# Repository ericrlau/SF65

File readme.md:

# SF65
## A ZMK-Powered BLE Keyboard with visible surface-mount components proudly displayed.

> :warning: **This is an untested project.** Do not use to create your own copy unless you are willing to debug the hardware and/or firmware. 

## Flash bootloader
Bootloader is pre-loaded on assembled pcbs. If you source your own BLE module you will need to unlock the module and flash the bootloader using the Nordic nrf command line tool. 
```
$ nrfjprog --recover --log 
```
```
$ nrfjprog -f nrf52 --program firmware/bootloader/COBO_nrf52840_bootloader-0.3.2-184-g64ea299_s140_6.1.1.hex
```

------------------------------------
## Upload Firmware 

- See ZMK docs for instructions on setting up ZMK and custimizing firmware.  
	* https://zmkfirmware.dev/docs/user-setup/
	* https://zmkfirmware.dev/docs/customization 
- Default *.uf2 files are pre-loaded on assembled pcbs. If you sourced and assembled your own pcb, you can file deafult pre-built firmware here: 
	- https://github.com/ericrlau/COBO-zmk-config/releases

## PCB
- Source files for pcb are in this repo. They are split into three kicad projects:
	- SF65: main pcb, left and right combined. 
	- (ToDo) SF65_Bottom: Bottom cover PCB. 
	- (ToDo) SF65_Plate: Switch plate PCB. 
	- NOTE: KiCad files are created with nightly KiCad 5.99 builds, they are not compatible with current stable release of KiCad 5.
- Bill of materials [Link](https://raw.githack.com/ericrlau/SF65/working/PCB/bom/ibom.html)

## ToDo 
- Test prototypes.
- Create switch plate.
- Create bottom Cover.
- Create bottom foot to angle board.
- Fix silk screen arrow on 1U key to right of spacebar. 

## Images

#### Prototype Build

#### Main PCB

#### FR4 Plate

#### Bottom PCB

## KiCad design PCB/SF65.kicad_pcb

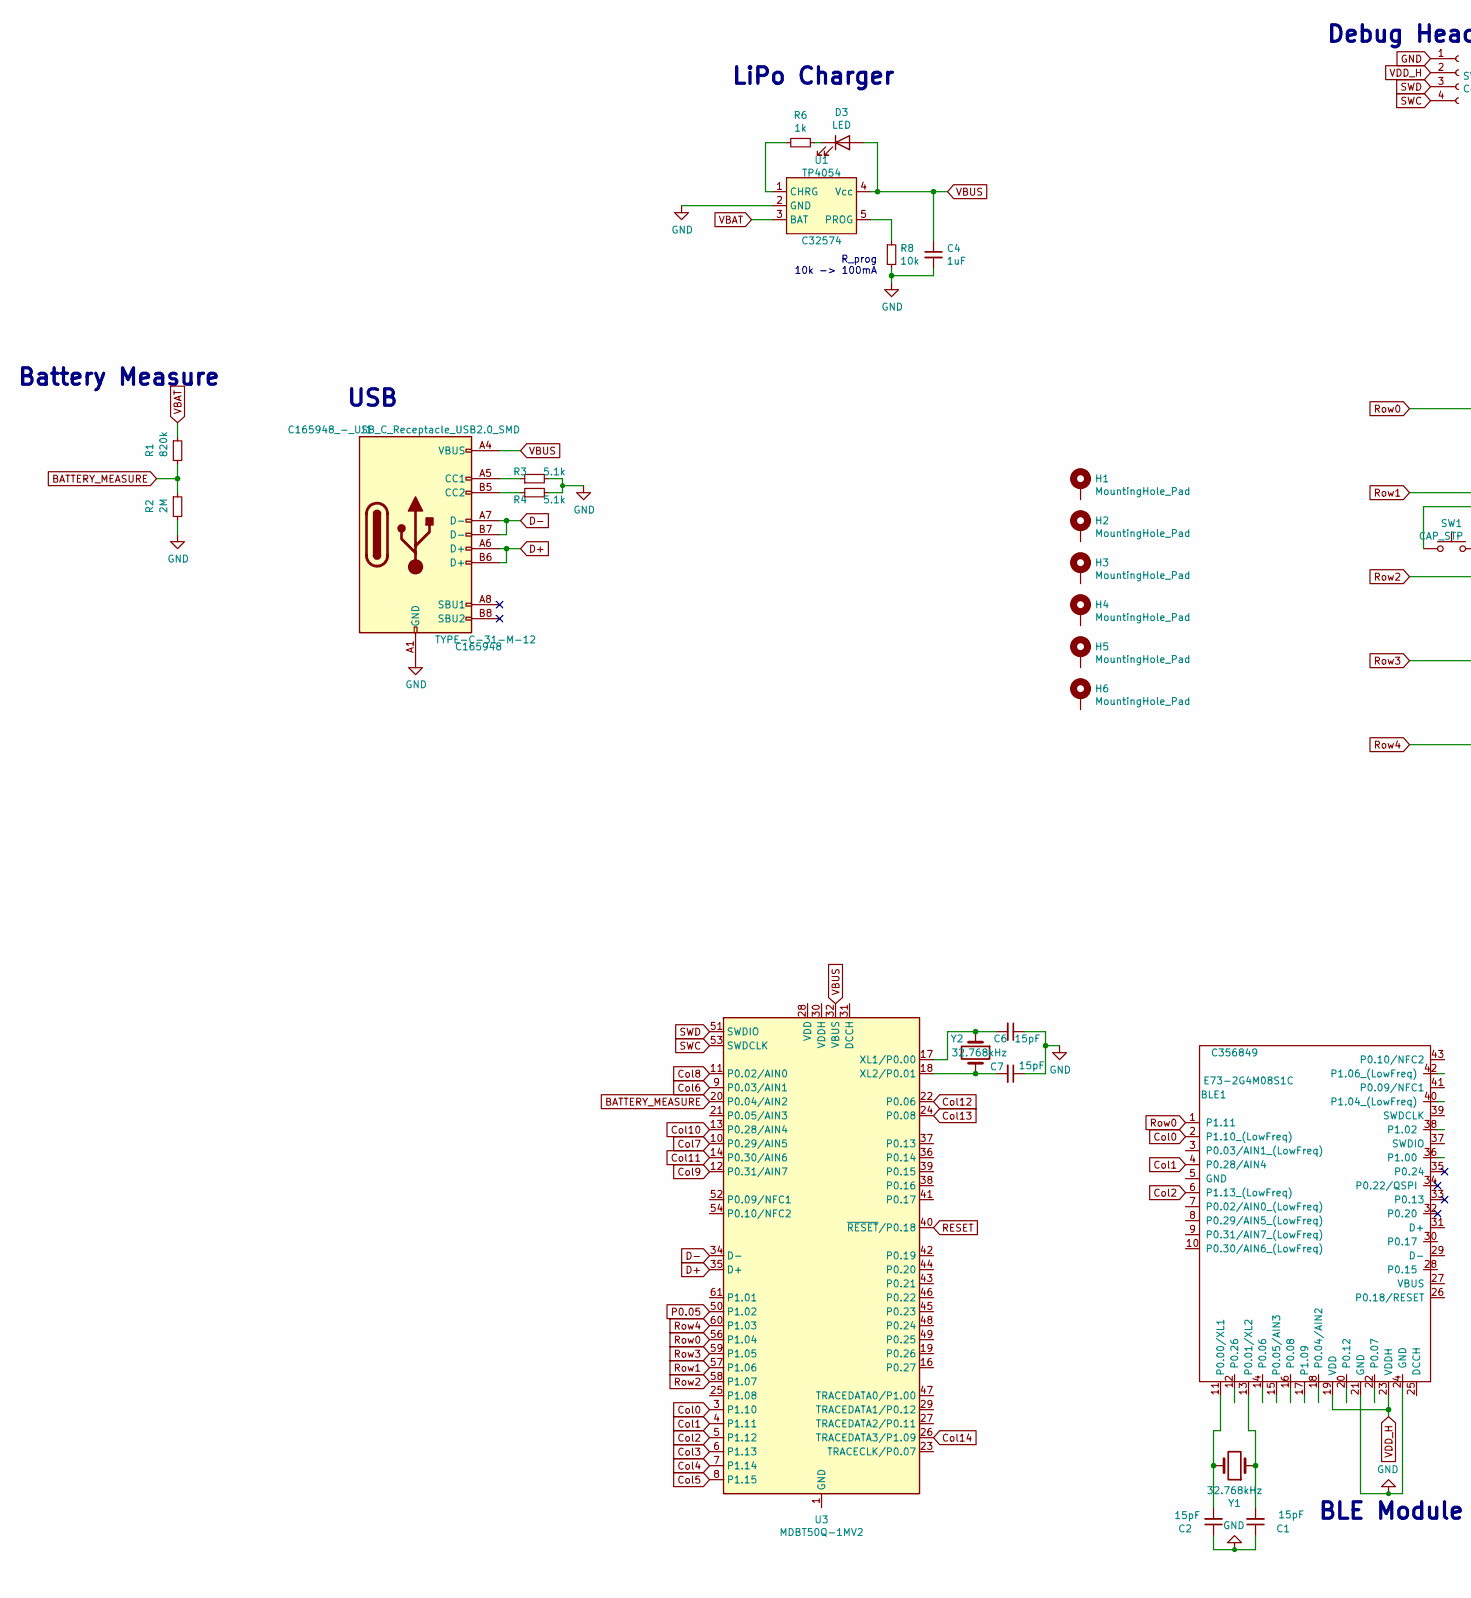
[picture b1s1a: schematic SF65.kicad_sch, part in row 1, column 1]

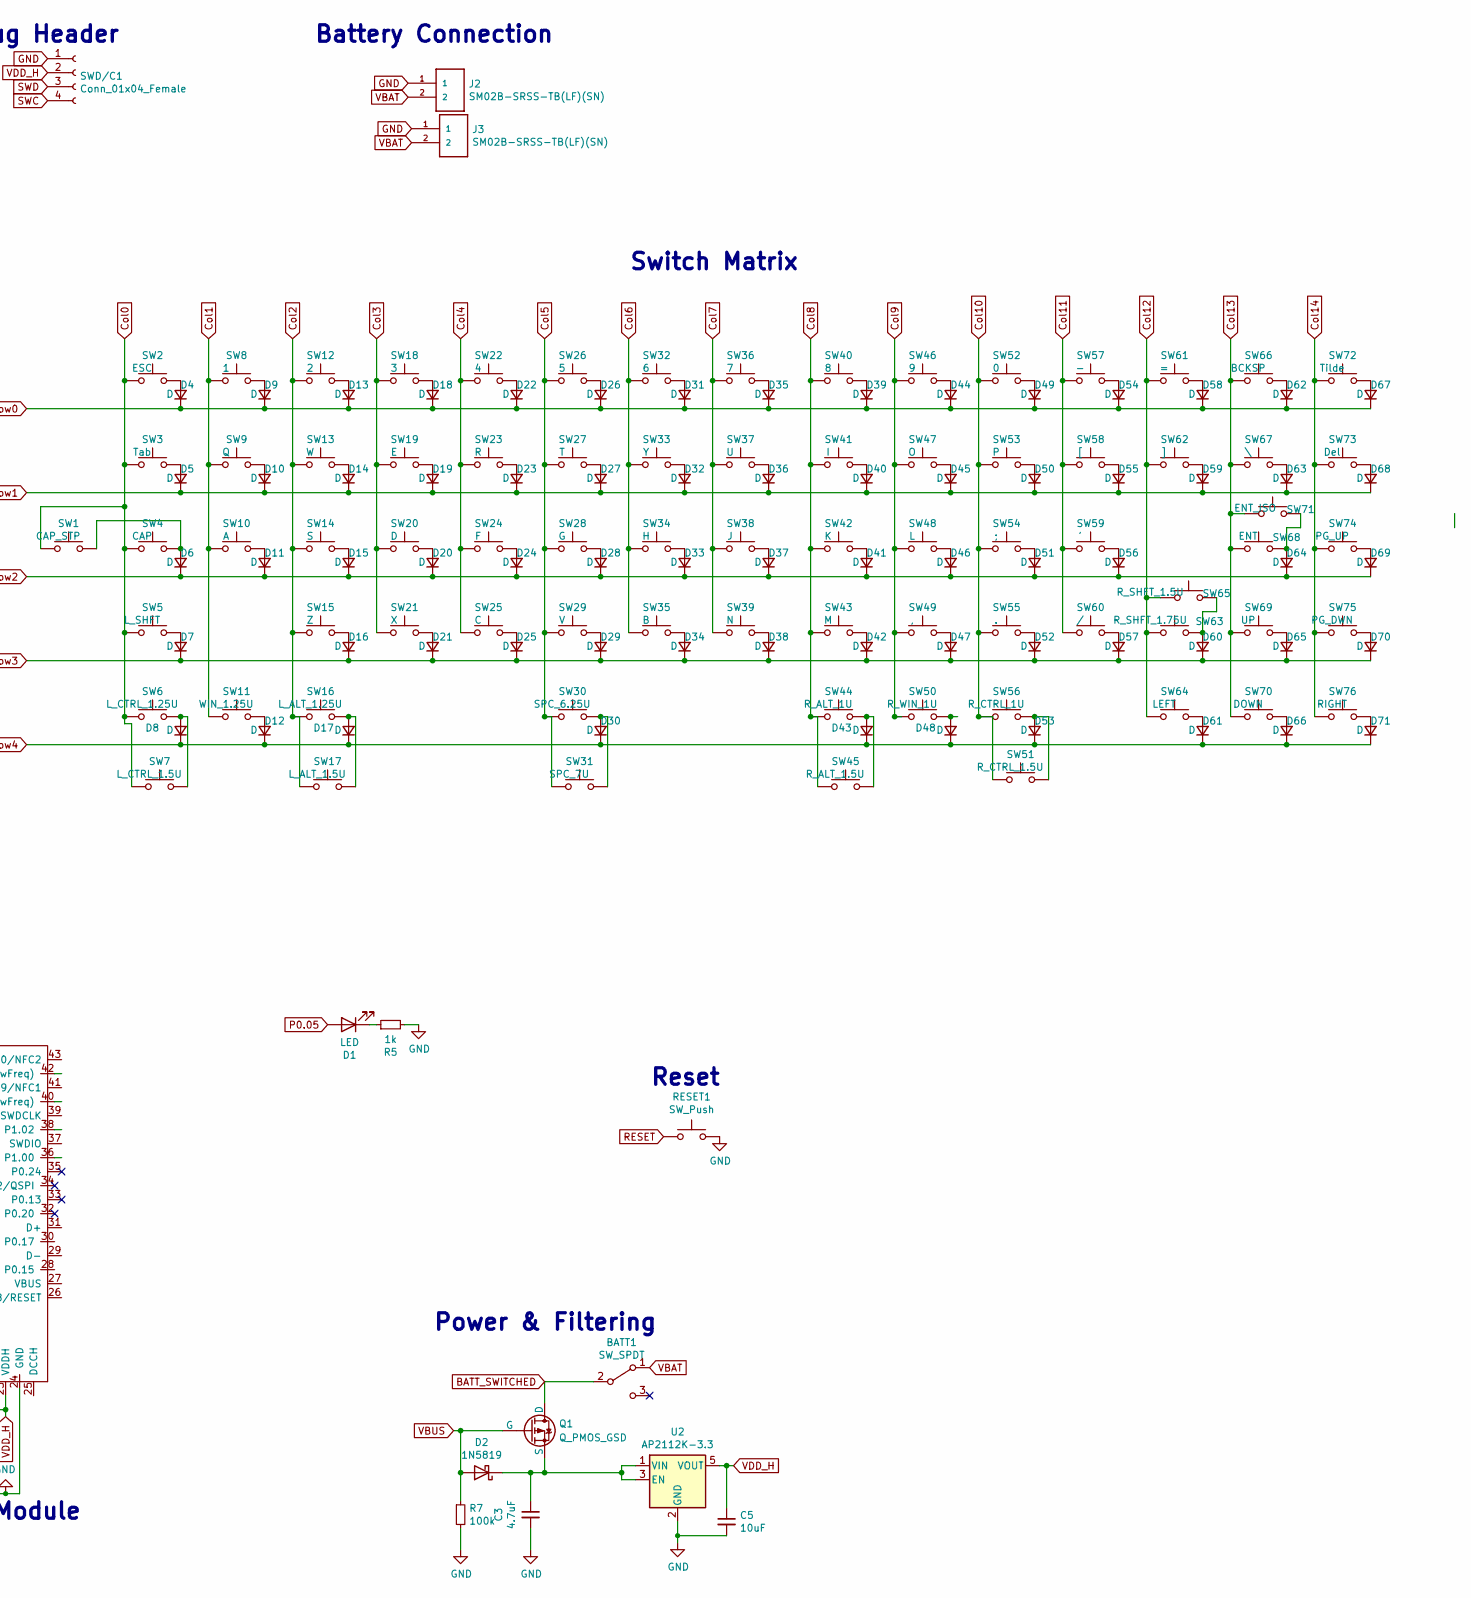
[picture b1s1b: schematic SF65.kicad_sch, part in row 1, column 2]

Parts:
BATT1: SW_SPDT; SW-TH_MSK12C02
BLE1: E73-2G4M08S1C; Manufacturer PN E73-2G4M08S1C; LCSC PN C356849
C1, C2, C6, C7: 15pF; C_0603_1608Metric
C3: 4.7uF; C_0603_1608Metric
C4: 1uF; C_0603_1608Metric
C5: 10uF; C_0603_1608Metric
D1, D3: LED; LED_0603_1608Metric_Pad1.05x0.95mm_HandSolder
D2: 1N5819; D_SOD-323_HandSoldering
D4, D5, D6, D7, D8, D9, D10, D11, D12, D13, D14, D15, D16, D17, D18, D19, D20, D21, D22, D23, D24, D25, D26, D27, D28, D29, D30, D31, D32, D33, D34, D35, D36, D37, D38, D39, D40, D41, D42, D43, D44, D45, D46, D47, D48, D49, D50, D51, D52, D53, D54, D55, D56, D57, D58, D59, D60, D61, D62, D63, D64, D65, D66, D67, D68, D69, D70, D71: D; D_SOD-123
H1, H2, H3, H4, H5, H6: MountingHole_Pad; MountingHole_2.2mm_M2
J1: C165948_-_USB_C_Receptacle_USB2.0_SMD; USB_C_Receptacle_HRO_TYPE-C-31-M-12; Manufacturer PN TYPE-C-31-M-12; LCSC PN C165948
J2: SM02B-SRSS-TB(LF)(SN)
J3: SM02B-SRSS-TB(LF)(SN); PinHeader_1x02_P2.54mm_Vertical
Q1: Q_PMOS_GSD; SOT-23
R1: 820k; R_0603_1608Metric_Pad0.98x0.95mm_HandSolder
R2: 2M; R_0603_1608Metric_Pad0.98x0.95mm_HandSolder
R3, R4: 5.1k; R_0603_1608Metric_Pad0.98x0.95mm_HandSolder
R5, R6: 1k; R_0603_1608Metric_Pad0.98x0.95mm_HandSolder
R7: 100k; R_0603_1608Metric_Pad0.98x0.95mm_HandSolder
R8: 10k; R_0603_1608Metric_Pad0.98x0.95mm_HandSolder
RESET1: SW_Push; SW_SPST_B3U-1000P
SW1: CAP_STP; MX_1.75U_STEPPEDCAPS
SW2: ESC; SW_Cherry_MX_1.00u_PCB
SW3: Tab; SW_Cherry_MX_1.50u_PCB
SW4: CAP; SW_Cherry_MX_1.75u_PCB
SW5: L_SHFT; SW_Cherry_MX_2.25u_PCB
SW6: L_CTRL_1.25U; SW_Cherry_MX_1.25u_PCB
SW7: L_CTRL_1.5U; SW_Cherry_MX_1.50u_PCB
SW8: 1; SW_Cherry_MX_1.00u_PCB
SW9: Q; SW_Cherry_MX_1.00u_PCB
SW10: A; SW_Cherry_MX_1.00u_PCB
SW11: WIN_1.25U; SW_Cherry_MX_1.25u_PCB
SW12: 2; SW_Cherry_MX_1.00u_PCB
SW13: W; SW_Cherry_MX_1.00u_PCB
SW14: S; SW_Cherry_MX_1.00u_PCB
SW15: Z; SW_Cherry_MX_1.00u_PCB
SW16: L_ALT_1.25U; SW_Cherry_MX_1.25u_PCB
SW17: L_ALT_1.5U; SW_Cherry_MX_1.50u_PCB
SW18: 3; SW_Cherry_MX_1.00u_PCB
SW19: E; SW_Cherry_MX_1.00u_PCB
SW20: D; SW_Cherry_MX_1.00u_PCB
SW21: X; SW_Cherry_MX_1.00u_PCB
SW22: 4; SW_Cherry_MX_1.00u_PCB
SW23: R; SW_Cherry_MX_1.00u_PCB
SW24: F; SW_Cherry_MX_1.00u_PCB
SW25: C; SW_Cherry_MX_1.00u_PCB
SW26: 5; SW_Cherry_MX_1.00u_PCB
SW27: T; SW_Cherry_MX_1.00u_PCB
SW28: G; SW_Cherry_MX_1.00u_PCB
SW29: V; SW_Cherry_MX_1.00u_PCB
SW30: SPC_6.25U; SW_Cherry_MX_6.25u_PCB
SW31: SPC_7U; MX_7U
SW32: 6; SW_Cherry_MX_1.00u_PCB
SW33: Y; SW_Cherry_MX_1.00u_PCB
SW34: H; SW_Cherry_MX_1.00u_PCB
SW35: B; SW_Cherry_MX_1.00u_PCB
SW36: 7; SW_Cherry_MX_1.00u_PCB
SW37: U; SW_Cherry_MX_1.00u_PCB
SW38: J; SW_Cherry_MX_1.00u_PCB
SW39: N; SW_Cherry_MX_1.00u_PCB
SW40: 8; SW_Cherry_MX_1.00u_PCB
SW41: I; SW_Cherry_MX_1.00u_PCB
SW42: K; SW_Cherry_MX_1.00u_PCB
SW43: M; SW_Cherry_MX_1.00u_PCB
SW44: R_ALT_1U; SW_Cherry_MX_1.00u_PCB
SW45: R_ALT_1.5U; SW_Cherry_MX_1.50u_PCB
SW46: 9; SW_Cherry_MX_1.00u_PCB
SW47: O; SW_Cherry_MX_1.00u_PCB
SW48: L; SW_Cherry_MX_1.00u_PCB
SW49: ,; SW_Cherry_MX_1.00u_PCB
SW50: R_WIN_1U; SW_Cherry_MX_1.00u_PCB
SW51: R_CTRL_1.5U; SW_Cherry_MX_1.50u_PCB
SW52: 0; SW_Cherry_MX_1.00u_PCB
SW53: P; SW_Cherry_MX_1.00u_PCB
SW54: ;; SW_Cherry_MX_1.00u_PCB
SW55: .; SW_Cherry_MX_1.00u_PCB
SW56: R_CTRL_1U; SW_Cherry_MX_1.00u_PCB
SW57: -; SW_Cherry_MX_1.00u_PCB
SW58: [; SW_Cherry_MX_1.00u_PCB
SW59: '; SW_Cherry_MX_1.00u_PCB
SW60: /; SW_Cherry_MX_1.00u_PCB
SW61: =; SW_Cherry_MX_1.00u_PCB
SW62: ]; SW_Cherry_MX_1.00u_PCB
SW63: R_SHFT_1.75U; SW_Cherry_MX_1.75u_PCB
SW64: LEFT; SW_Cherry_MX_1.00u_PCB
SW65: R_SHFT_1.5U; SW_Cherry_MX_1.50u_PCB
SW66: BCKSP; SW_Cherry_MX_2.00u_PCB
SW67: \; SW_Cherry_MX_1.50u_PCB
SW68: ENT; SW_Cherry_MX_2.25u_PCB
SW69: UP; SW_Cherry_MX_1.00u_PCB
SW70: DOWN; SW_Cherry_MX_1.00u_PCB
SW71: ENT_ISO; SW_Cherry_MX_ISOEnter_PCB
SW72: Tilde; SW_Cherry_MX_1.00u_PCB
SW73: Del; SW_Cherry_MX_1.00u_PCB
SW74: PG_UP; SW_Cherry_MX_1.00u_PCB
SW75: PG_DWN; SW_Cherry_MX_1.00u_PCB
SW76: RIGHT; SW_Cherry_MX_1.00u_PCB
SWD/C1: Conn_01x04_Female; PinHeader_1x04_P2.54mm_Vertical
U1: TP4054; SOT-23-5; Manufacturer PN TP4054; LCSC PN C32574
U2: AP2112K-3.3; SOT-23-5
U3: MDBT50Q-1MV2; Raytac_MDBT50Q
Y1, Y2: 32.768kHz; FC-135R_L3.2-W1.5

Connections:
BATTERY_MEASURE: R1.2, R2.1, U3.20 (P0.04/AIN2)
BATT_SWITCHED: BATT1.2 (B), Q1.3 (D)
Col0: BLE1.2 (P1.10_(LowFreq)), SW1.1, SW2.1, SW3.1, SW4.1, SW5.1, SW6.1, SW7.1, U3.3 (P1.10)
Col1: BLE1.4 (P0.28/AIN4), SW8.1, SW9.1, SW10.1, SW11.1, U3.4 (P1.11)
Col2: BLE1.6 (P1.13_(LowFreq)), SW12.1, SW13.1, SW14.1, SW15.1, SW16.1, SW17.1, U3.5 (P1.12)
Col3: SW18.1, SW19.1, SW20.1, SW21.1, U3.6 (P1.13)
Col4: SW22.1, SW23.1, SW24.1, SW25.1, U3.7 (P1.14)
Col5: SW26.1, SW27.1, SW28.1, SW29.1, SW30.1, SW31.1, U3.8 (P1.15)
Col6: SW32.1, SW33.1, SW34.1, SW35.1, U3.9 (P0.03/AIN1)
Col7: SW36.1, SW37.1, SW38.1, SW39.1, U3.10 (P0.29/AIN5)
Col8: SW40.1, SW41.1, SW42.1, SW43.1, SW44.1, SW45.1, U3.11 (P0.02/AIN0)
Col9: SW46.1, SW47.1, SW48.1, SW49.1, SW50.1, U3.12 (P0.31/AIN7)
Col10: SW51.1, SW52.1, SW53.1, SW54.1, SW55.1, SW56.1, U3.13 (P0.28/AIN4)
Col11: SW57.1, SW58.1, SW59.1, SW60.1, U3.14 (P0.30/AIN6)
Col12: SW61.1, SW62.1, SW63.1, SW64.1, SW65.1, U3.22 (P0.06)
Col13: SW66.1, SW67.1, SW68.1, SW69.1, SW70.1, SW71.1, U3.24 (P0.08)
Col14: SW72.1, SW73.1, SW74.1, SW75.1, SW76.1, U3.26 (TRACEDATA3/P1.09)
D+: J1.A6 (D+), J1.B6 (D+), U3.35 (D+); also elsewhere on the board
D-: J1.A7 (D-), J1.B7 (D-), U3.34 (D-); also elsewhere on the board
GND: BLE1.21 (GND), BLE1.24 (GND), C1.1, C2.1, C3.2, C4.2, C5.2, C6.1, C7.1, J1.A1 (GND), J1.A12 (GND), J1.B1 (GND), J1.B12 (GND), J2.1, J3.1, R2.2, R3.2, R4.2, R5.2, R7.2, R8.2, RESET1.2, SWD/C1.1, U1.2 (GND), U2.2 (GND); also elsewhere on the board
unnamed: BLE1.11 (P0.00/XL1), C2.2, Y1.2
unnamed: BLE1.13 (P0.01/XL2), C1.2, Y1.1
unnamed: C3.1, D2.1 (K), Q1.2 (S), U2.1 (VIN), U2.3 (EN)
unnamed: C6.2, U3.17 (XL1/P0.00), Y2.1
unnamed: C7.2, U3.18 (XL2/P0.01), Y2.2
unnamed: D1.1 (K), R5.1
unnamed: D3.1 (K), R6.1
unnamed: D4.2 (A), SW2.2
unnamed: D5.2 (A), SW3.2
unnamed: D6.2 (A), SW1.2, SW4.2
unnamed: D7.2 (A), SW5.2
unnamed: D8.2 (A), SW6.2, SW7.2
unnamed: D9.2 (A), SW8.2
unnamed: D10.2 (A), SW9.2
unnamed: D11.2 (A), SW10.2
unnamed: D12.2 (A), SW11.2
unnamed: D13.2 (A), SW12.2
unnamed: D14.2 (A), SW13.2
unnamed: D15.2 (A), SW14.2
unnamed: D16.2 (A), SW15.2
unnamed: D17.2 (A), SW16.2, SW17.2
unnamed: D18.2 (A), SW18.2
unnamed: D19.2 (A), SW19.2
unnamed: D20.2 (A), SW20.2
unnamed: D21.2 (A), SW21.2
unnamed: D22.2 (A), SW22.2
unnamed: D23.2 (A), SW23.2
unnamed: D24.2 (A), SW24.2
unnamed: D25.2 (A), SW25.2
unnamed: D26.2 (A), SW26.2
unnamed: D27.2 (A), SW27.2
unnamed: D28.2 (A), SW28.2
unnamed: D29.2 (A), SW29.2
unnamed: D30.2 (A), SW30.2, SW31.2
unnamed: D31.2 (A), SW32.2
unnamed: D32.2 (A), SW33.2
unnamed: D33.2 (A), SW34.2
unnamed: D34.2 (A), SW35.2
unnamed: D35.2 (A), SW36.2
unnamed: D36.2 (A), SW37.2
unnamed: D37.2 (A), SW38.2
unnamed: D38.2 (A), SW39.2
unnamed: D39.2 (A), SW40.2
unnamed: D40.2 (A), SW41.2
unnamed: D41.2 (A), SW42.2
unnamed: D42.2 (A), SW43.2
unnamed: D43.2 (A), SW44.2, SW45.2
unnamed: D44.2 (A), SW46.2
unnamed: D45.2 (A), SW47.2
unnamed: D46.2 (A), SW48.2
unnamed: D47.2 (A), SW49.2
unnamed: D48.2 (A), SW50.2
unnamed: D49.2 (A), SW52.2
unnamed: D50.2 (A), SW53.2
unnamed: D51.2 (A), SW54.2
unnamed: D52.2 (A), SW55.2
unnamed: D53.2 (A), SW51.2, SW56.2
unnamed: D54.2 (A), SW57.2
unnamed: D55.2 (A), SW58.2
unnamed: D56.2 (A), SW59.2
unnamed: D57.2 (A), SW60.2
unnamed: D58.2 (A), SW61.2
unnamed: D59.2 (A), SW62.2
unnamed: D60.2 (A), SW63.2, SW65.2
unnamed: D61.2 (A), SW64.2
unnamed: D62.2 (A), SW66.2
unnamed: D63.2 (A), SW67.2
unnamed: D64.2 (A), SW68.2, SW71.2
unnamed: D65.2 (A), SW69.2
unnamed: D66.2 (A), SW70.2
unnamed: D67.2 (A), SW72.2
unnamed: D68.2 (A), SW73.2
unnamed: D69.2 (A), SW74.2
unnamed: D70.2 (A), SW75.2
unnamed: D71.2 (A), SW76.2
unnamed 95: J1.A5 (CC1), R3.1; also elsewhere on the board
unnamed 96: J1.B5 (CC2), R4.1; also elsewhere on the board
unnamed: R6.2, U1.1 (CHRG)
unnamed: R8.1, U1.5 (PROG)
unnamed: U3.1 (GND), U3.2 (GND), U3.15 (GND), U3.33 (GND), U3.55 (GND)
P0.05: D1.2 (A), U3.50 (P1.02)
RESET: RESET1.1, U3.40 (~RESET~/P0.18); also elsewhere on the board
Row0: BLE1.1 (P1.11), D4.1 (K), D9.1 (K), D13.1 (K), D18.1 (K), D22.1 (K), D26.1 (K), D31.1 (K), D35.1 (K), D39.1 (K), D44.1 (K), D49.1 (K), D54.1 (K), D58.1 (K), D62.1 (K), D67.1 (K), U3.56 (P1.04)
Row1: D5.1 (K), D10.1 (K), D14.1 (K), D19.1 (K), D23.1 (K), D27.1 (K), D32.1 (K), D36.1 (K), D40.1 (K), D45.1 (K), D50.1 (K), D55.1 (K), D59.1 (K), D63.1 (K), D68.1 (K), U3.57 (P1.06)
Row2: D6.1 (K), D11.1 (K), D15.1 (K), D20.1 (K), D24.1 (K), D28.1 (K), D33.1 (K), D37.1 (K), D41.1 (K), D46.1 (K), D51.1 (K), D56.1 (K), D64.1 (K), D69.1 (K), U3.58 (P1.07)
Row3: D7.1 (K), D16.1 (K), D21.1 (K), D25.1 (K), D29.1 (K), D34.1 (K), D38.1 (K), D42.1 (K), D47.1 (K), D52.1 (K), D57.1 (K), D60.1 (K), D65.1 (K), D70.1 (K), U3.59 (P1.05)
Row4: D8.1 (K), D12.1 (K), D17.1 (K), D30.1 (K), D43.1 (K), D48.1 (K), D53.1 (K), D61.1 (K), D66.1 (K), D71.1 (K), U3.60 (P1.03)
SWC: SWD/C1.4, U3.53 (SWDCLK); also elsewhere on the board
SWD: SWD/C1.3, U3.51 (SWDIO); also elsewhere on the board
VBAT: BATT1.1 (A), J2.2, J3.2, R1.1, U1.3 (BAT)
VBUS: C4.1, D2.2 (A), D3.2 (A), J1.A4 (VBUS), J1.A9 (VBUS), J1.B4 (VBUS), J1.B9 (VBUS), Q1.1 (G), R7.1, U1.4 (Vcc), U3.32 (VBUS); also elsewhere on the board
VDD_H: BLE1.19 (VDD), BLE1.23 (VDDH), C5.1, SWD/C1.2, U2.5 (VOUT); also elsewhere on the board

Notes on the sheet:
Battery Measure
USB
LiPo Charger
R_prog 10k -> 100mA
Debug Header
BLE Module
Battery Connection
Power & Filtering
Switch Matrix
Reset

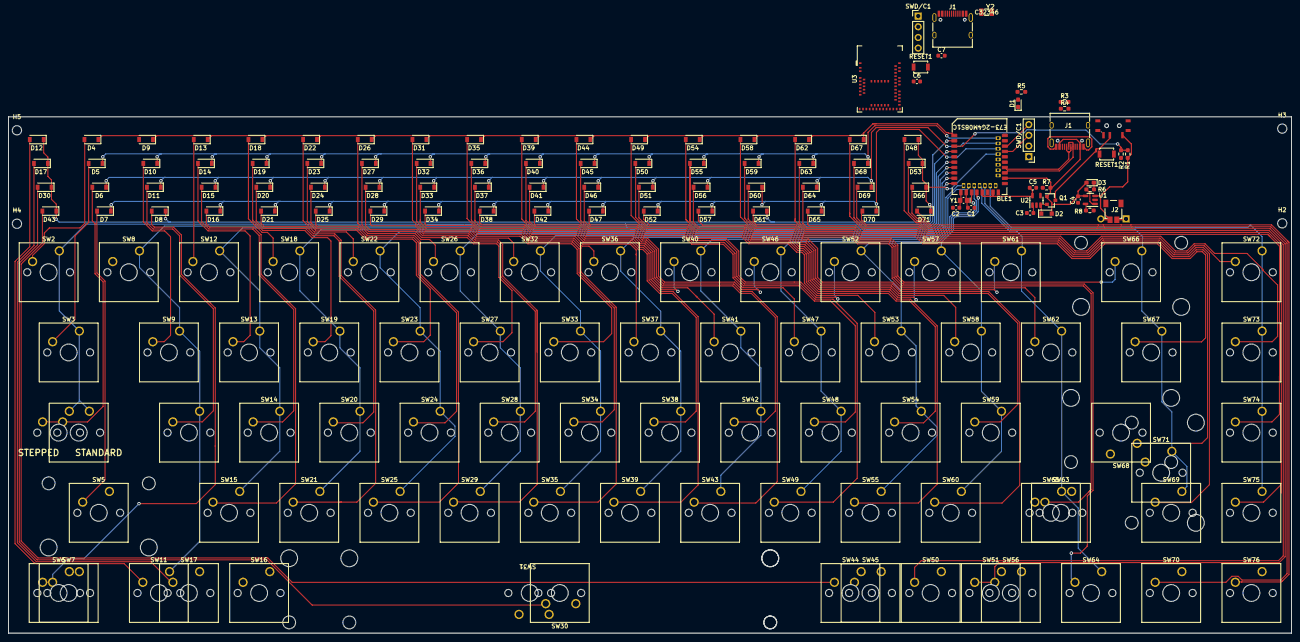
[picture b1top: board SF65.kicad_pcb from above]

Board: 2 copper layers, 304.8 x 122.6 mm, 184 parts (0 on the bottom side), 112 nets.

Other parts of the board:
J1#2: C165948_-_USB_C_Receptacle_USB2.0_SMD; USB_C_Receptacle_HRO_TYPE-C-31-M-12
RESET1#2: SW_Push; SW_SPST_B3U-1000P
SWD/C1#2: Conn_01x04_Female; PinHeader_1x04_P2.54mm_Vertical

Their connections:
D+: J1#2.A6 (D+), J1#2.B6 (D+); also elsewhere on the board
D-: J1#2.A7 (D-), J1#2.B7 (D-); also elsewhere on the board
GND: J1#2.A1 (GND), J1#2.A12 (GND), J1#2.B1 (GND), J1#2.B12 (GND), RESET1#2.2, SWD/C1#2.1; also elsewhere on the board
unnamed 95: J1#2.A5 (CC1); also elsewhere on the board
unnamed 96: J1#2.B5 (CC2); also elsewhere on the board
RESET: RESET1#2.1; also elsewhere on the board
SWC: SWD/C1#2.4; also elsewhere on the board
SWD: SWD/C1#2.3; also elsewhere on the board
VBUS: J1#2.A4 (VBUS), J1#2.A9 (VBUS), J1#2.B4 (VBUS), J1#2.B9 (VBUS); also elsewhere on the board
VDD_H: SWD/C1#2.2; also elsewhere on the board

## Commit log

2021-02-01 initial
2021-02-03 diodes placed
2021-02-07 working on routing, not complete
2021-02-28 about to swap in raytac module
2021-03-07 order SF65 samples from JLC
2021-03-21 cleanup and readme
2021-04-18 starting to make v2 edits, not finished
